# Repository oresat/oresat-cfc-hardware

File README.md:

# oresat-cfc-hardware

Cirrrus Flux Camera hardware repository. See also https://www.oresat.org/satellites/oresat/mission-2-cfc.

## General information
The Cirrus Flux Camera (CFC) is a Short Wave Infrared (SWIR) camera meant to map the global distribution of high-altitude cirrus clouds. It works by looking at the reflected sunlight from clouds in three SWIR bands. The primary investigators (PIs) for CFC calibration, data processing, and climate science are our collaborators at the [University of Maryland Baltimore Count (UMBC)'s Earth and Space Institute (ESI)](https://esi.umbc.edu/) as well as by our collaborators at the [University College London (UCL) Mullard Space Science Laboratory (MSSL)](https://www.ucl.ac.uk/mathematical-physical-sciences/mssl).

Older versions of the CFC flew on the [2022 NASA High Altitude Student Payload (HASP)](https://sg-webserver.phys.lsu.edu/) mission.

Different but modern versions were flown by [UMBC's AirHARP mission](https://esi.umbc.edu/airharp2-at-pace-pax/) on the NASA ER-2 high altitude plane.

Most recently, we flew a preliminary technology demonstration mission on [OreSat0.5](https://www.oresat.org/satellites/oresat0-5) launched August 16th, 2024.

We're planning on flying the science mission camera on OreSat1 in Q2 2026.

Versions of the CFC have also flown on the NASA High Altitude Student Payload (HASP) in New Mexico, and 
## Technical information about the CFC sensor

- Princeton IR PIRT1280 InGaAs focal plane array (1280 x 1024 with 12 um pixels), sensitive to roughly 800 - 1600 nm.
- We cool the sensor to -8 deg C using its built-in thermal electric cooler (TEC - just a standard Peltier device).
- We use three filters on the PIRT1280 sensors:
   - 870 nm: [Torrent Photonics Optical Filter Shop 2020OFS-870](https://opticalfiltershop.com/shop/bandpass-filter/nir-bandpass-700nm-to-1100nm/nir-bandpass-filter-870nm-fwhm-30nm/)
   - 1390 nm: [Torrent Photonics Optical Filter Shop 2020OFS-1390](https://opticalfiltershop.com/shop/bandpass-filter/swir-bandpass-filters-1-1um-to-3-0um/swir-bandpass-filter-1390nm-fwhm-35nm/)
   - 1590 nm: [Torrent Photonics Optical Filter Shop 2020OFS-1590](https://opticalfiltershop.com/shop/bandpass-filter/swir-bandpass-filters-1-1um-to-3-0um/swir-bandpass-filter-1590nm-fwhm-40nm/)
- Lens is the [Navitar SWIR-35](https://store.navitar.com/swir-35-35-mm/), a 35 mm  SWIR lens with focus adjustable apateur. 

## Technical information on the system

- The **CFC Sensor Card** is a PCB in backplane slot 18. It has:
   - The PIRT 1280 sensor soldered on the PCB
   - A custom machined lens adapter between the card and the lens.
   - Custom machined G10 L brackets between the custom machined lens adapter and slot 19 
   - The lens on the adapter sticks through the -Z end card, through the -Z end cap, and finally out into the tuna can volume. A 3D printed adapter on the End Card holds the monopole deployers and holds the camera lens at the End Card and End Cap levels.
   - The SWIR lens sticks into the tuna-can space on the -Z end of OreSat0.5 and OreSat1.
- The **CFC Processor Card** is a PCB in backplane slot 17 with:
   - LVDS to PRU adapter IC
   - an [Octavo OSD335x-SM](https://octavosystems.com/octavo_products/osd335x-sm/) system in package (SIP) processor with 1 GB DRAM and a 16 GB eMMC storage IC.
 - Radiator
    - The top of the CFC Sensor Card has a large block of copper being used as a heat spreader. The heat spreader dumps the heat from the TEC into thin copper leaf springs that lead the heat to two external copper radiators in the -Z+Y and -Z-Y solar module positions. These copper radiators are covered by a high emissivity tape.
    
## Design Notes

- Mostly on our Google Drive right now, here's the beginnings of our [CFC Design Notes](https://docs.google.com/document/d/1nDrTuUim9k1om3DOcBtnp3ixVvrmmALAsb2CZlDwwio/edit?usp=sharing).

## Links to CAD

- [OreSat CFC Camera mechnical in OnShape](https://cad.onshape.com/documents/0e986a82427039a7549eafca/v/f54f3484c685a75ab5bd82ce/e/deddd282159689e0e52f600b)
- [OreSat0.5 containing the CFC assembly in OnShape](https://cad.onshape.com/documents/c0a6cf3367d8fdcad3a3c2e1/w/ca55e3ec6f041493d70e4b39/e/591851cdc8c634aae1522f90)
- [Electronics CAD on Github](https://github.com/oresat/oresat-cfc-hardware) - mostly KiCad with some older EAGLE files.
- [Kernel module](https://github.com/oresat/oresat-prucam-pirt1280) for the PIRT 1280 on the Octavo's PRU.

## License

All materials in this repo are copyright Portland State Aerospace Society and are licensed under the CERN Open Hardware Licence Version 2 -
Strongly Reciprocal (CERN-OHL-S v2), or any later version. A copy of the license is located in [here](LICENSE.md).

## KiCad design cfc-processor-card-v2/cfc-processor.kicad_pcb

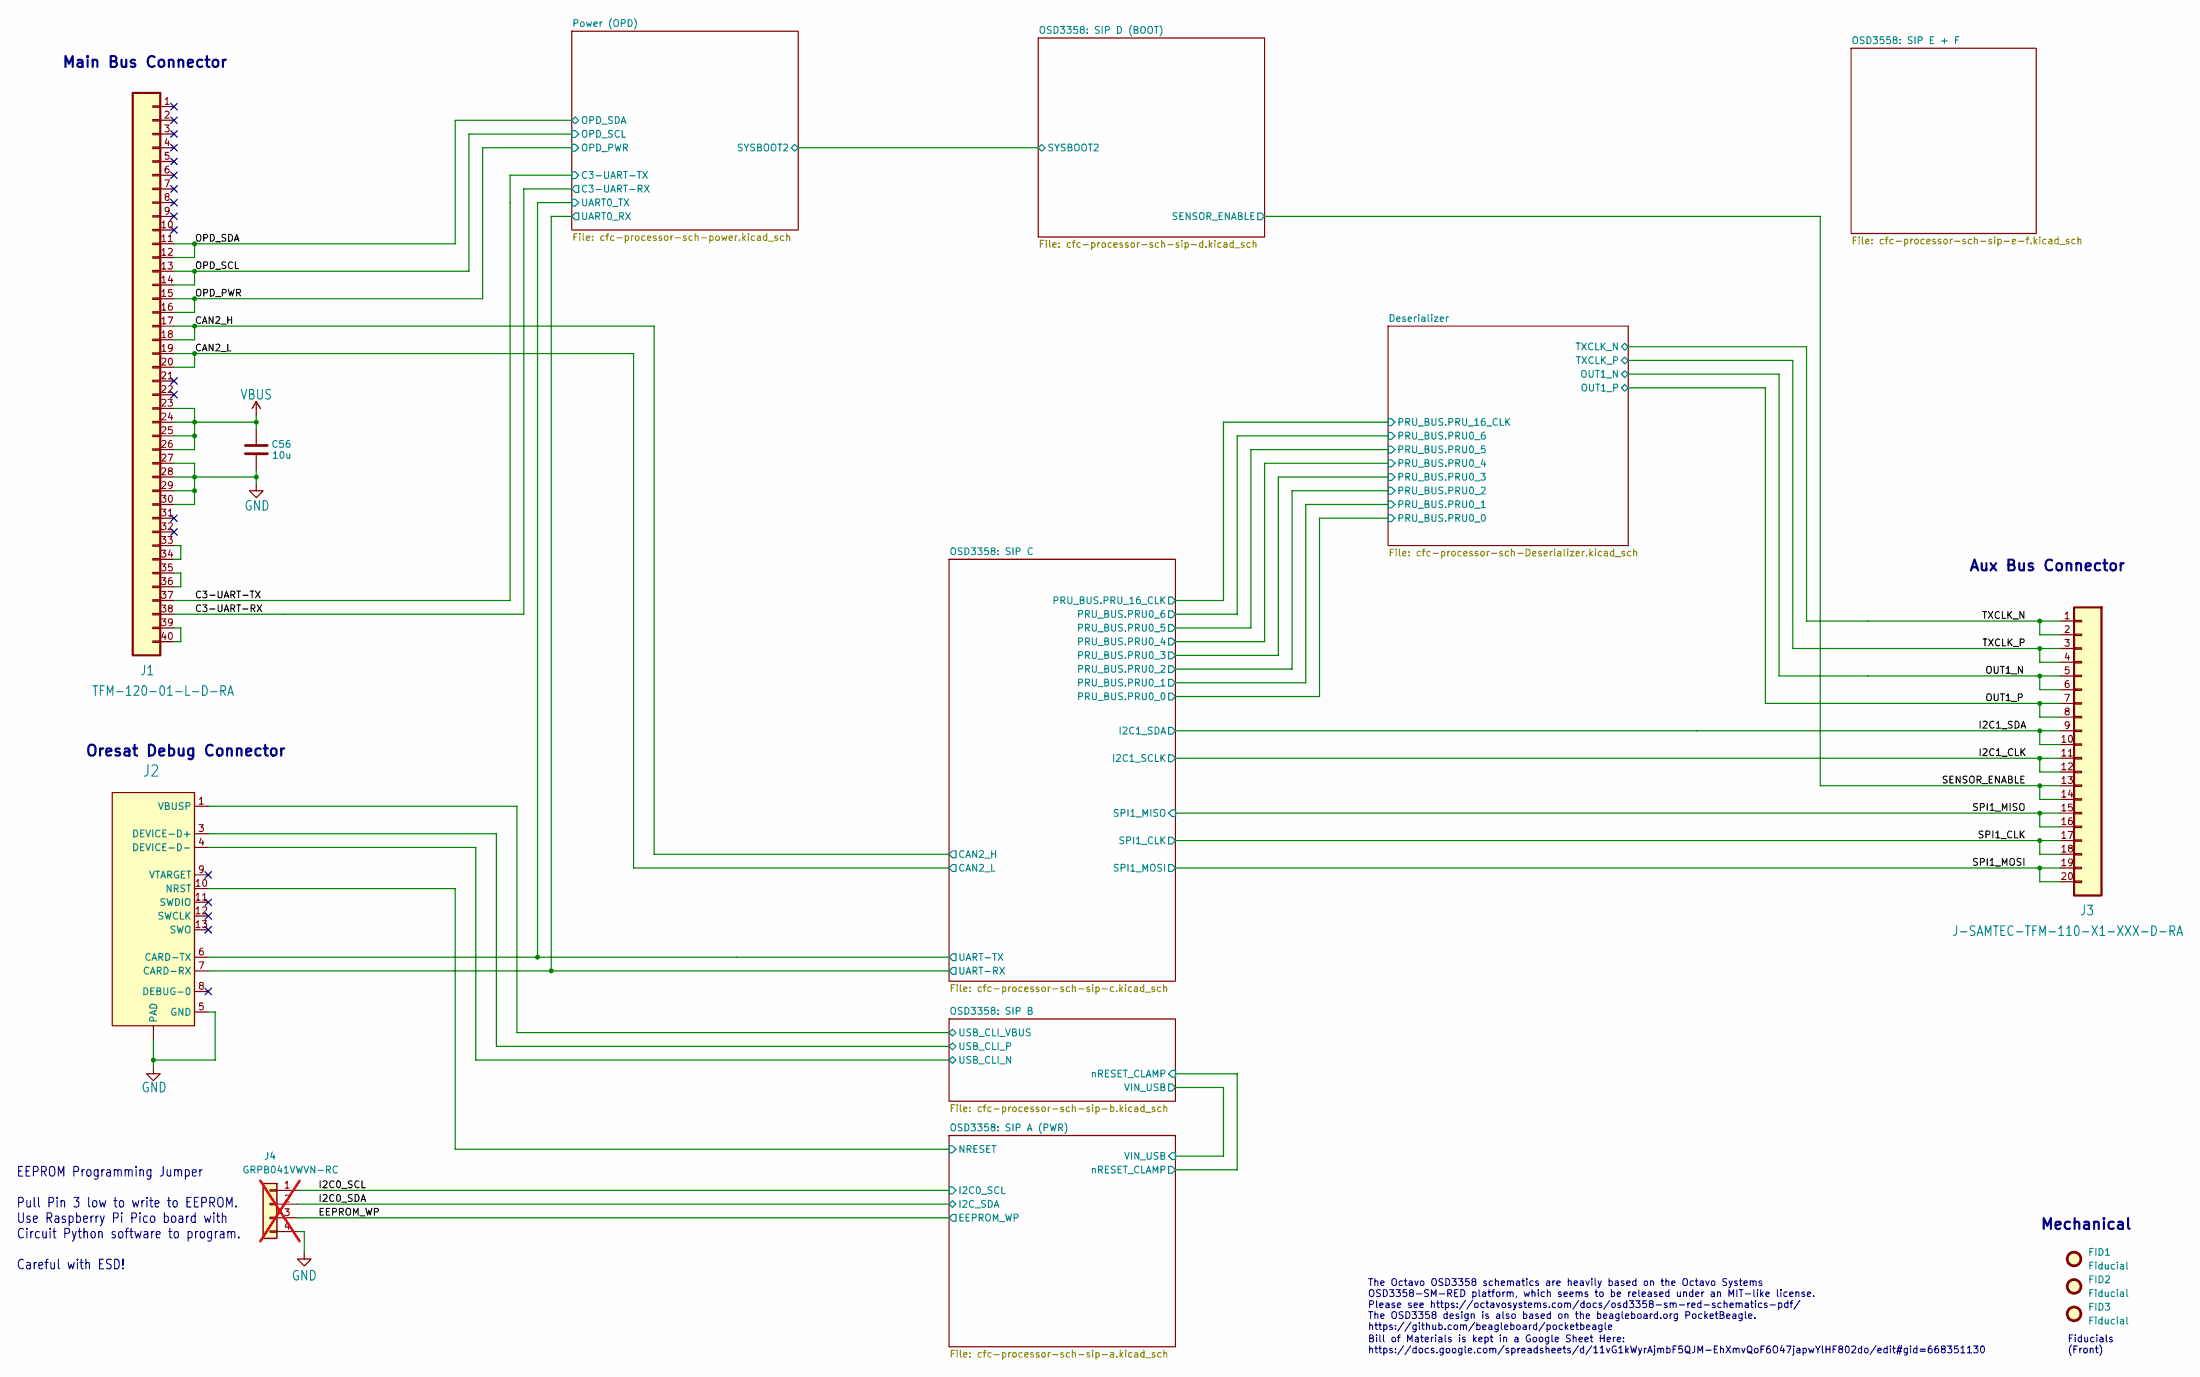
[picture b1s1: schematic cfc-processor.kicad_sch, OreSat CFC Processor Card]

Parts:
C56: 10u; 0805-B-NOSILK; MPN CL21B106KAYQNNE
FID1, FID2, FID3: Fiducial; Fiducial_1mm_Mask2mm
J1: TFM-120-01-L-D-RA; J-SAMTEC-TFM-120-X1-XXX-D-RA; MPN TFM-120-01-L-D-RA
J2: 2-1734592-0; J-JST-SM14BSHLSTF; MPN SM14B-SHLS-TF
J3: J-SAMTEC-TFM-110-X1-XXX-D-RA; MPN TFM-110-01-L-D-RA
J4: GRPB041VWVN-RC; PinHeader_1x04_P1.27mm_Vertical; MPN GRPB041VWVN-RC; not fitted

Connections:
/C3-UART-RX: J1.38; also elsewhere on the board
/C3-UART-TX: J1.37; also elsewhere on the board
/CAN2_H: J1.17, J1.18; also elsewhere on the board
/CAN2_L: J1.19, J1.20; also elsewhere on the board
/EEPROM_WP: J4.3; also elsewhere on the board
/I2C0_SCL: J4.1; also elsewhere on the board
/I2C0_SDA: J4.2; also elsewhere on the board
/I2C1_CLK: J3.11, J3.12; also elsewhere on the board
/I2C1_SDA: J3.9, J3.10; also elsewhere on the board
/OPD_PWR: J1.15, J1.16; also elsewhere on the board
/OPD_SCL: J1.13, J1.14; also elsewhere on the board
/OPD_SDA: J1.11, J1.12; also elsewhere on the board
/OSD3358: SIP A (PWR)/NRESET: J2.10 (NRST); also elsewhere on the board
/OSD3358: SIP B/USB_CLI_N: J2.4 (DEVICE-D-); also elsewhere on the board
/OSD3358: SIP B/USB_CLI_P: J2.3 (DEVICE-D+); also elsewhere on the board
/OSD3358: SIP B/USB_CLI_VBUS: J2.1 (VBUSP), J2.2 (VBUSP); also elsewhere on the board
/OSD3358: SIP C/UART-RX: J2.7 (CARD-RX); also elsewhere on the board
/OSD3358: SIP C/UART-TX: J2.6 (CARD-TX); also elsewhere on the board
/OUT1_N: J3.5, J3.6; also elsewhere on the board
/OUT1_P: J3.7, J3.8; also elsewhere on the board
/SENSOR_ENABLE: J3.13, J3.14; also elsewhere on the board
/SPI1_CLK: J3.17, J3.18; also elsewhere on the board
/SPI1_MISO: J3.15, J3.16; also elsewhere on the board
/SPI1_MOSI: J3.19, J3.20; also elsewhere on the board
/TXCLK_N: J3.1, J3.2; also elsewhere on the board
/TXCLK_P: J3.3, J3.4; also elsewhere on the board
GND: C56.2, J1.27, J1.28, J1.29, J1.30, J2.5 (GND), J2.14 (GND), J2.15 (PAD), J2.16 (PAD), J4.4; also elsewhere on the board
unnamed: J1.33, J1.34
unnamed: J1.35, J1.36
unnamed: J1.39, J1.40
VBUS: C56.1, J1.23, J1.24, J1.25, J1.26; also elsewhere on the board

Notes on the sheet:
Bill of Materials is kept in a Google Sheet Here: https://docs.google.com/spreadsheets/d/11vG1kWyrAjmbF5QJM-EhXmvQoF6O47japwYlHF802do/edit#gid=668351130
EEPROM Programming Jumper Pull Pin 3 low to write to EEPROM. Use Raspberry Pi Pico board with Circuit Python software to program. Careful with ESD!
The OSD3358 design is also based on the beagleboard.org PocketBeagle. https://github.com/beagleboard/pocketbeagle
Mechanical
Fiducials (Front)
Main Bus Connector
The Octavo OSD3358 schematics are heavily based on the Octavo Systems OSD3358-SM-RED platform, which seems to be released under an MIT-like license. Please see https://octavosystems.com/docs/osd3358-sm-red-schematics-pdf/
Aux Bus Connector
Oresat Debug Connector

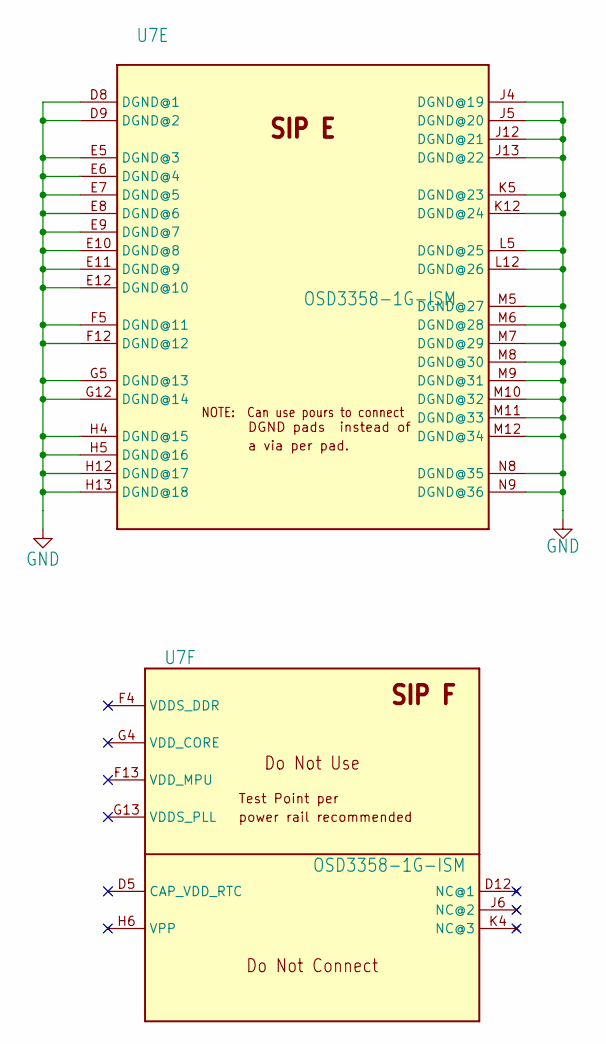
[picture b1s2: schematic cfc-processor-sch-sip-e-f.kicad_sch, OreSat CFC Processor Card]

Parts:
U7: OSD3358-1G-ISM; U-Octavo-OSD335X-BGA-256; MPN OSD3358-1G-ISM

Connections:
GND: U7.D8 (DGND@1), U7.D9 (DGND@2), U7.E5 (DGND@3), U7.E6 (DGND@4), U7.E7 (DGND@5), U7.E8 (DGND@6), U7.E9 (DGND@7), U7.E10 (DGND@8), U7.E11 (DGND@9), U7.E12 (DGND@10), U7.F5 (DGND@11), U7.F12 (DGND@12), U7.G5 (DGND@13), U7.G12 (DGND@14), U7.H4 (DGND@15), U7.H5 (DGND@16), U7.H12 (DGND@17), U7.H13 (DGND@18), U7.J4 (DGND@19), U7.J5 (DGND@20), U7.J12 (DGND@21), U7.J13 (DGND@22), U7.K5 (DGND@23), U7.K12 (DGND@24), U7.L5 (DGND@25), U7.L12 (DGND@26), U7.M5 (DGND@27), U7.M6 (DGND@28), U7.M7 (DGND@29), U7.M8 (DGND@30), U7.M9 (DGND@31), U7.M10 (DGND@32), U7.M11 (DGND@33), U7.M12 (DGND@34), U7.N8 (DGND@35), U7.N9 (DGND@36); also elsewhere on the board

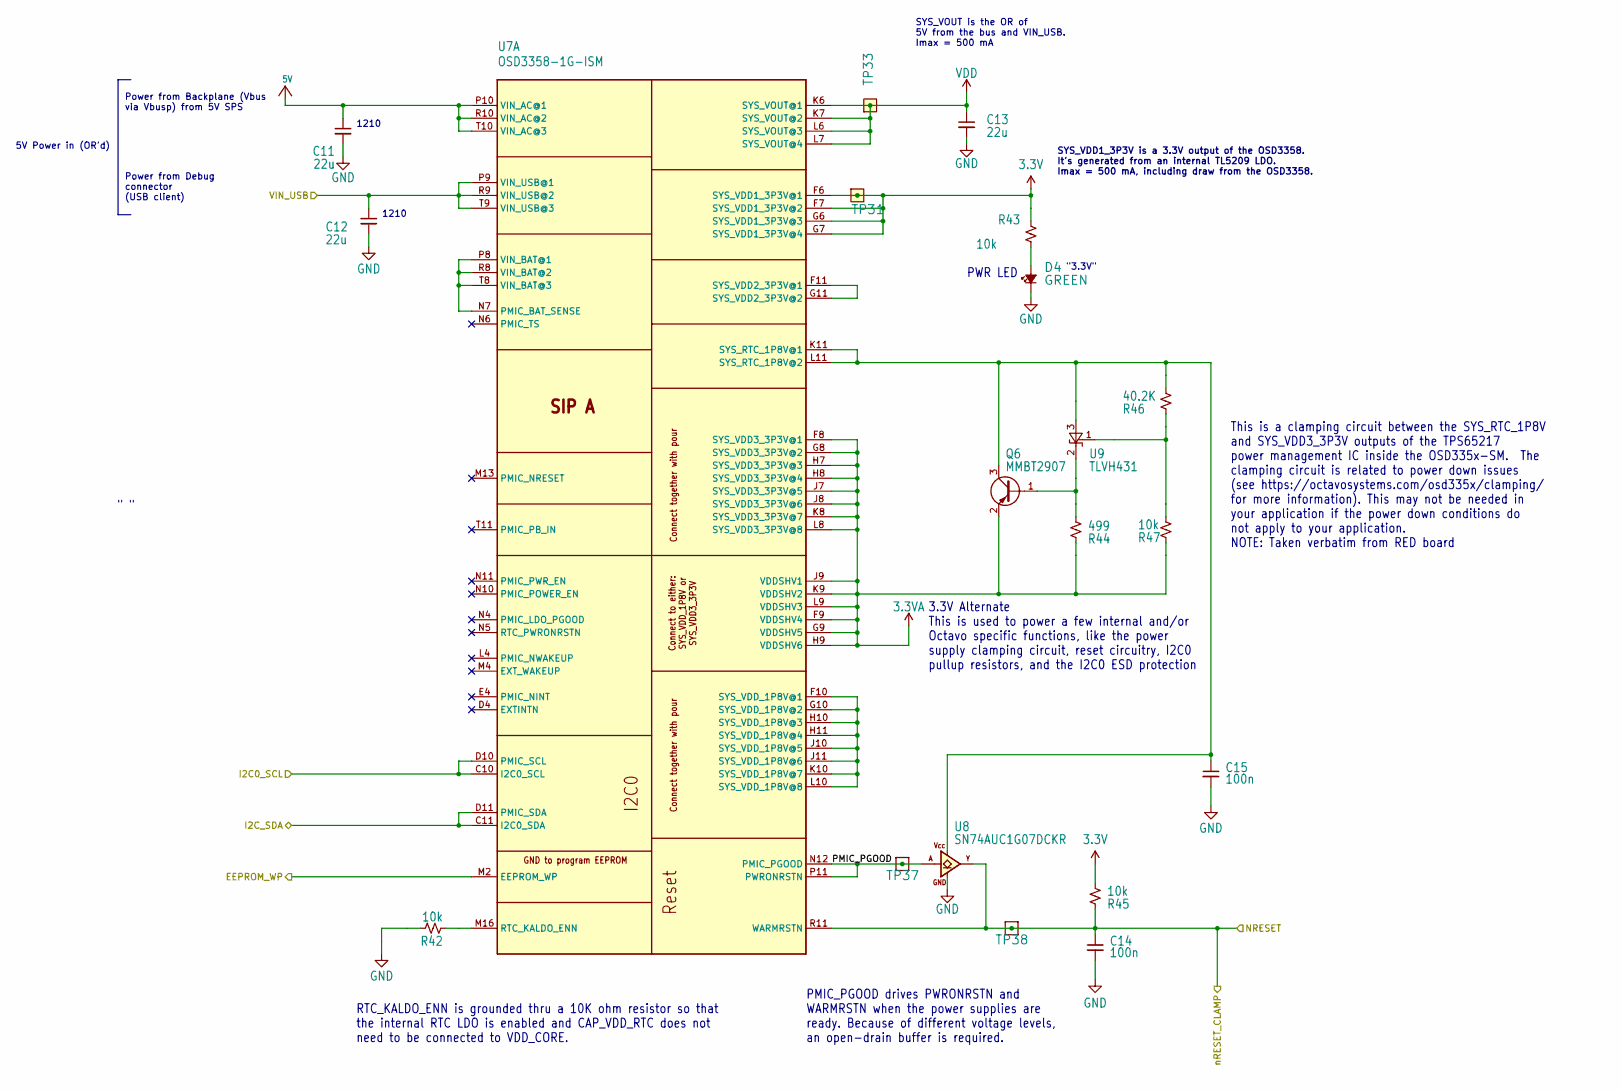
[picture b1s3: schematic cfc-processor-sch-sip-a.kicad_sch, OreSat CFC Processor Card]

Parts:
C11, C12, C13: 22u; C_1210_3225Metric; MPN TMK325B7226KMHP
C14, C15: 100n; 0603-C-NOSILK; MPN C0603C104K5RACAUTO
D4: GREEN; LED_0603_1608Metric; MPN 150060GS75000
Q6: MMBT2907; SOT-23; MPN PMBT2907A,235
R42, R43, R45, R47: 10k; 0603-C-NOSILK; MPN RMCF0603FT10K0
R44: 499; 0603-C-NOSILK; MPN RMCF0603FT499R
R46: 40.2K; 0603-C-NOSILK; MPN RMCF0603FT40K2
TP31: TEST-POINT; TestPoint-0.75mm-th
TP33: TEST-POINT3X4; TestPoint-0.75mm-th
TP37, TP38: TEST-POINT3X4; TestPoint_Pad_D1.0mm
U7: OSD3358-1G-ISM; U-Octavo-OSD335X-BGA-256; MPN OSD3358-1G-ISM
U8: SN74AUC1G07DCKR; SOT-353_SC-70-5; MPN SN74AUC1G07DCKR
U9: TLVH431; SOT-23; MPN TLVH431BCDBZT

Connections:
3.3V: R43.1, R45.1, TP31.1 (1_1), U7.F6 (SYS_VDD1_3P3V@1), U7.F7 (SYS_VDD1_3P3V@2), U7.G6 (SYS_VDD1_3P3V@3), U7.G7 (SYS_VDD1_3P3V@4); also elsewhere on the board
3.3VA: Q6.2 (E), R44.2, R47.2, U7.F8 (SYS_VDD3_3P3V@1), U7.F9 (VDDSHV4), U7.G8 (SYS_VDD3_3P3V@2), U7.G9 (VDDSHV5), U7.H7 (SYS_VDD3_3P3V@3), U7.H8 (SYS_VDD3_3P3V@4), U7.H9 (VDDSHV6), U7.J7 (SYS_VDD3_3P3V@5), U7.J8 (SYS_VDD3_3P3V@6), U7.J9 (VDDSHV1), U7.K8 (SYS_VDD3_3P3V@7), U7.K9 (VDDSHV2), U7.L8 (SYS_VDD3_3P3V@8), U7.L9 (VDDSHV3)
5V: C11.1, U7.P10 (VIN_AC@1), U7.R10 (VIN_AC@2), U7.T10 (VIN_AC@3); also elsewhere on the board
/EEPROM_WP: U7.M2 (EEPROM_WP); also elsewhere on the board
/I2C0_SCL: U7.C10 (I2C0_SCL), U7.D10 (PMIC_SCL); also elsewhere on the board
/I2C0_SDA: U7.C11 (I2C0_SDA), U7.D11 (PMIC_SDA); also elsewhere on the board
/OSD3358: SIP A (PWR)/NRESET: C14.1, R45.2, TP38.1 (1_1), U7.R11 (WARMRSTN), U8.4 (Y); also elsewhere on the board
/OSD3358: SIP A (PWR)/PMIC_PGOOD: TP37.1 (1_1), U7.N12 (PMIC_PGOOD), U7.P11 (PWRONRSTN), U8.2 (A)
/OSD3358: SIP A (PWR)/VIN_USB: C12.1, U7.P9 (VIN_USB@1), U7.R9 (VIN_USB@2), U7.T9 (VIN_USB@3); also elsewhere on the board
GND: C11.2, C12.2, C13.2, C14.2, C15.2, D4.1 (K), R42.1, U8.3 (GND); also elsewhere on the board
unnamed: D4.2 (A), R43.2
unnamed: Q6.1 (B), R44.1, U9.2 (K)
unnamed: C15.1, Q6.3 (C), R46.1, U7.K11 (SYS_RTC_1P8V@1), U7.L11 (SYS_RTC_1P8V@2), U8.5 (VCC), U9.3 (A)
unnamed: U7.N7 (PMIC_BAT_SENSE), U7.P8 (VIN_BAT@1), U7.R8 (VIN_BAT@2), U7.T8 (VIN_BAT@3)
unnamed: R42.2, U7.M16 (RTC_KALDO_ENN)
unnamed: U7.F11 (SYS_VDD2_3P3V@1), U7.G11 (SYS_VDD2_3P3V@2)
unnamed: U7.F10 (SYS_VDD_1P8V@1), U7.G10 (SYS_VDD_1P8V@2), U7.H10 (SYS_VDD_1P8V@3), U7.H11 (SYS_VDD_1P8V@4), U7.J10 (SYS_VDD_1P8V@5), U7.J11 (SYS_VDD_1P8V@6), U7.K10 (SYS_VDD_1P8V@7), U7.L10 (SYS_VDD_1P8V@8)
unnamed: R46.2, R47.1, U9.1 (REF)
VDD: C13.1, TP33.1 (1_1), U7.K6 (SYS_VOUT@1), U7.K7 (SYS_VOUT@2), U7.L6 (SYS_VOUT@3), U7.L7 (SYS_VOUT@4)

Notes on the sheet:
SYS_VDD1_3P3V is a 3.3V output of the OSD3358. It's generated from an internal TL5209 LDO. Imax = 500 mA, including draw from the OSD3358.
PMIC_PGOOD drives PWRONRSTN and WARMRSTN when the power supplies are ready. Because of different voltage levels, an open-drain buffer is required.
" "
5V Power in (OR'd)
RTC_KALDO_ENN is grounded thru a 10K ohm resistor so that the internal RTC LDO is enabled and CAP_VDD_RTC does not need to be connected to VDD_CORE.
This is a clamping circuit between the SYS_RTC_1P8V and SYS_VDD3_3P3V outputs of the TPS65217 power management IC inside the OSD335x-SM. The clamping circuit is related to power down issues (see https://octavosystems.com/osd335x/clamping/ for more information). This may not be needed in your applic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
"3.3V"
PWR LED
1210
SYS_VOUT is the OR of 5V from the bus and VIN_USB. Imax = 500 mA
Power from Debug connector (USB client)
3.3V Alternate This is used to power a few internal and/or Octavo specific functions, like the power supply clamping circuit, reset circuitry, I2C0 pullup resistors, and the I2C0 ESD protection
Power from Backplane (Vbus via Vbusp) from 5V SPS

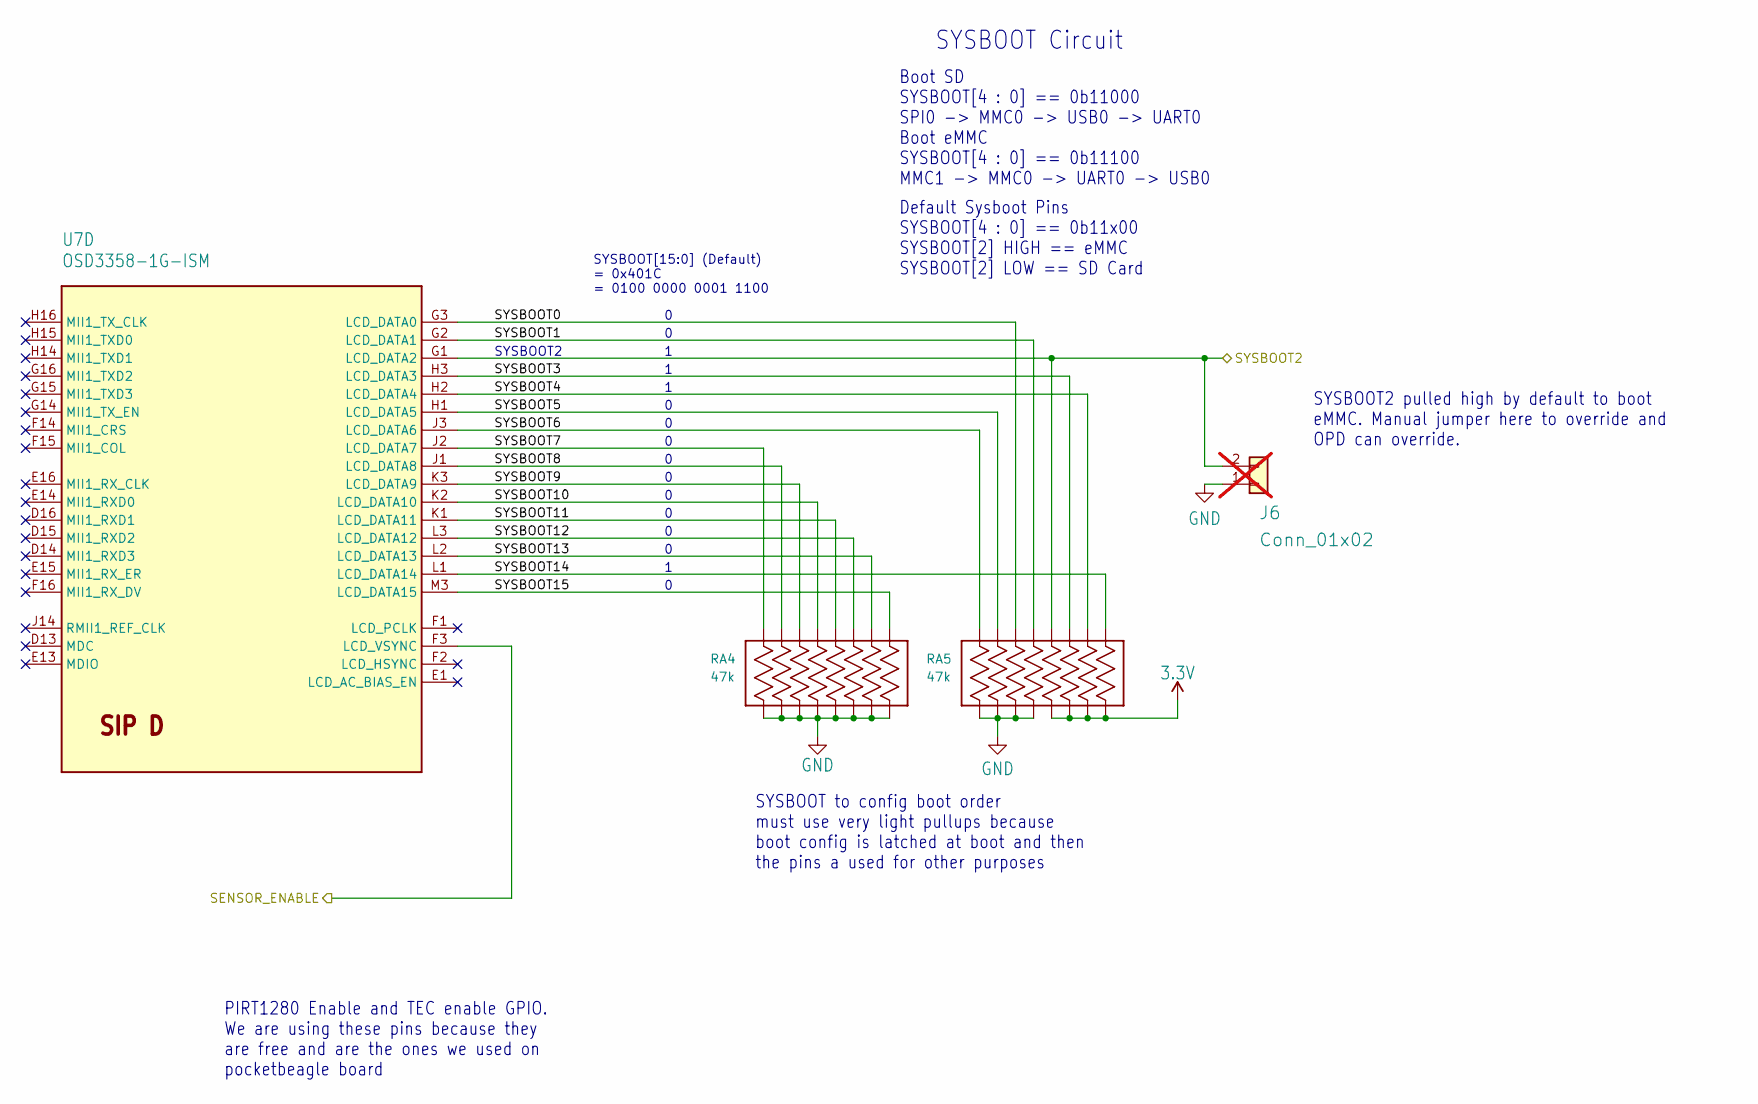
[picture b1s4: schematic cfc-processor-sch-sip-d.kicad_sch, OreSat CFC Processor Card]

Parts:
J6: Conn_01x02; PinHeader_1x02_P2.54mm_Vertical; not fitted
RA4, RA5: 47k; RES_EXB2HV; MPN EXB-2HV473JV
U7: OSD3358-1G-ISM; U-Octavo-OSD335X-BGA-256; MPN OSD3358-1G-ISM

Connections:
3.3V: RA5.5, RA5.6, RA5.7, RA5.8; also elsewhere on the board
/OSD3358: SIP D (BOOT)/SYSBOOT0: RA5.14, U7.G3 (LCD_DATA0)
/OSD3358: SIP D (BOOT)/SYSBOOT1: RA5.13, U7.G2 (LCD_DATA1)
/OSD3358: SIP D (BOOT)/SYSBOOT2: J6.2, RA5.12, U7.G1 (LCD_DATA2); also elsewhere on the board
/OSD3358: SIP D (BOOT)/SYSBOOT3: RA5.11, U7.H3 (LCD_DATA3)
/OSD3358: SIP D (BOOT)/SYSBOOT4: RA5.10, U7.H2 (LCD_DATA4)
/OSD3358: SIP D (BOOT)/SYSBOOT5: RA5.15, U7.H1 (LCD_DATA5)
/OSD3358: SIP D (BOOT)/SYSBOOT6: RA5.16, U7.J3 (LCD_DATA6)
/OSD3358: SIP D (BOOT)/SYSBOOT7: RA4.16, U7.J2 (LCD_DATA7)
/OSD3358: SIP D (BOOT)/SYSBOOT8: RA4.15, U7.J1 (LCD_DATA8)
/OSD3358: SIP D (BOOT)/SYSBOOT9: RA4.14, U7.K3 (LCD_DATA9)
/OSD3358: SIP D (BOOT)/SYSBOOT10: RA4.13, U7.K2 (LCD_DATA10)
/OSD3358: SIP D (BOOT)/SYSBOOT11: RA4.12, U7.K1 (LCD_DATA11)
/OSD3358: SIP D (BOOT)/SYSBOOT12: RA4.11, U7.L3 (LCD_DATA12)
/OSD3358: SIP D (BOOT)/SYSBOOT13: RA4.10, U7.L2 (LCD_DATA13)
/OSD3358: SIP D (BOOT)/SYSBOOT14: RA5.9, U7.L1 (LCD_DATA14)
/OSD3358: SIP D (BOOT)/SYSBOOT15: RA4.9, U7.M3 (LCD_DATA15)
/SENSOR_ENABLE: U7.F3 (LCD_VSYNC); also elsewhere on the board
GND: J6.1, RA4.1, RA4.2, RA4.3, RA4.4, RA4.5, RA4.6, RA4.7, RA4.8, RA5.1, RA5.2, RA5.3, RA5.4; also elsewhere on the board

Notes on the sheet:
PIRT1280 Enable and TEC enable GPIO. We are using these pins because they are free and are the ones we used on pocketbeagle board
SYSBOOT Circuit
SYSBOOT[15:0] (Default) = 0x401C = 0100 0000 0001 1100
Boot SD SYSBOOT[4 : 0] == 0b11000 SPI0 -> MMC0 -> USB0 -> UART0 Boot eMMC SYSBOOT[4 : 0] == 0b11100 MMC1 -> MMC0 -> UART0 -> USB0
Default Sysboot Pins SYSBOOT[4 : 0] == 0b11x00 SYSBOOT[2] HIGH == eMMC SYSBOOT[2] LOW == SD Card
SYSBOOT to config boot order must use very light pullups because boot config is latched at boot and then the pins a used for other purposes
SYSBOOT2 pulled high by default to boot eMMC. Manual jumper here to override and OPD can override.
SYSBOOT2

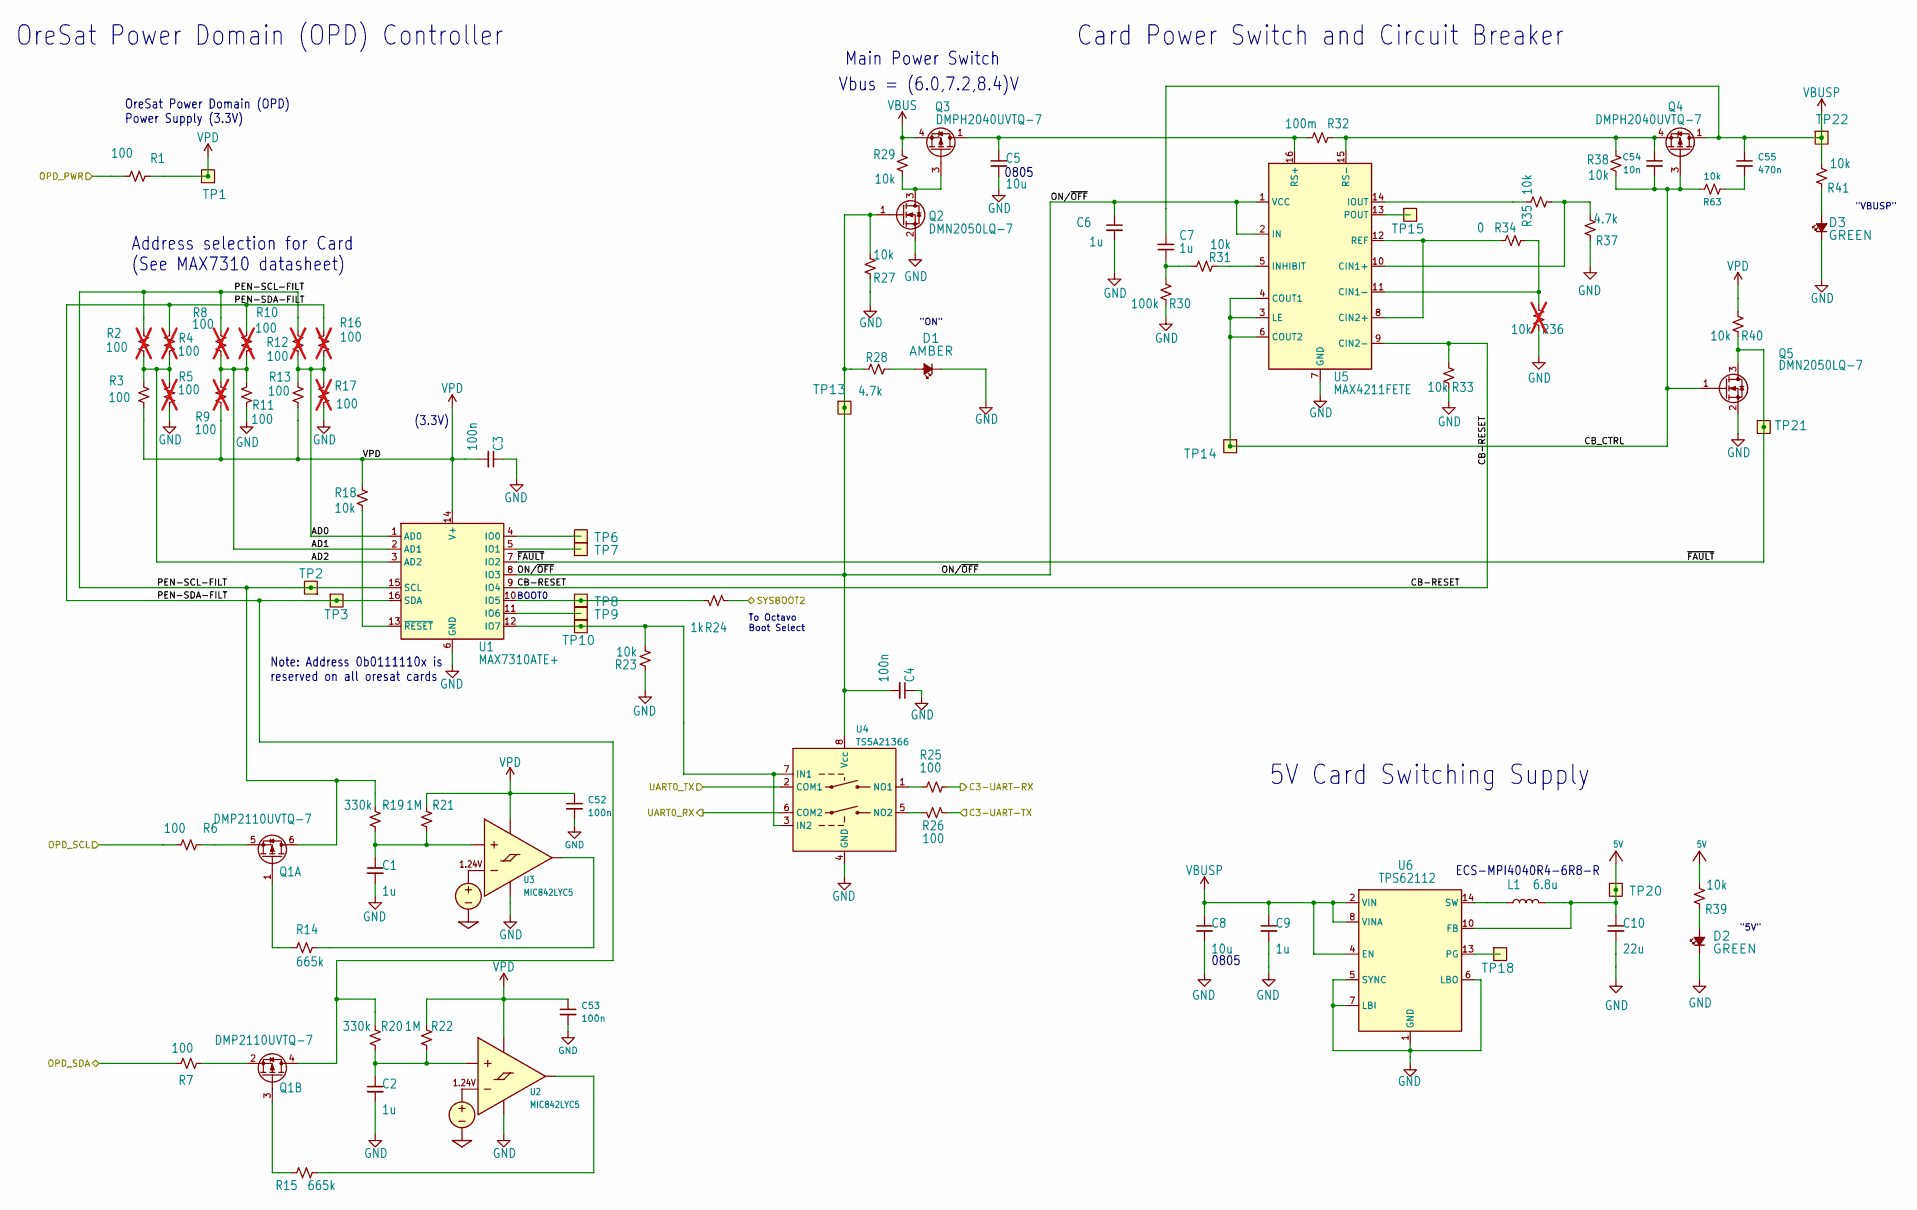
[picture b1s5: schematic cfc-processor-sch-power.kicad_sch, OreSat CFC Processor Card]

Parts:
C1, C2, C6, C7, C9: 1u; 0603-C-NOSILK; MPN GCM21BR71H105KA03L
C3, C4, C52, C53: 100n; 0603-C-NOSILK; MPN C0603C104K5RACAUTO
C5, C8: 10u; 0805-C-NOSILK; MPN GRT21BC71E106KE13K
C10: 22u; C_1210_3225Metric; MPN TMK325B7226KMHP
C54: 10n; 0603-C-NOSILK; MPN C0603C103J5RACAUTO
C55: 470n; 0603-C-NOSILK; MPN C0603C474K3RACAUTO
D1: AMBER; LED_0603_1608Metric; MPN 150060AS75000
D2, D3: GREEN; LED_0603_1608Metric; MPN 150060GS75000
L1: 6.8u; L_ECS-MPI4040; MPN ECS-MPI4040R4-6R8-R
Q1: DMP2110UVTQ-7; SOT-23-6; MPN DMP2110UVTQ-7
Q2, Q5: DMN2050LQ-7; SOT-23; MPN DMN2050LQ-7
Q3, Q4: DMPH2040UVTQ-7; TSOT-23-6; MPN DMPH2040UVTQ-7
R1, R3, R6, R7, R11, R13, R25, R26: 100; 0603-C-NOSILK; MPN RMCF0603FT100R
R2, R4, R5, R8, R9, R10, R12, R16, R17: 100; 0603-C-NOSILK; MPN RMCF0603FT100R; not fitted
R14, R15: 665k; 0603-C-NOSILK; MPN RMCF0603FT665K
R18, R23, R27, R29, R31, R33, R35, R38, R39, R40, R41, R63: 10k; 0603-C-NOSILK; MPN RMCF0603FT10K0
R19, R20: 330k; 0603-C-NOSILK; MPN RMCF0603FT330K
R21, R22: 1M; 0603-C-NOSILK; MPN RMCF0603FG1M00
R24: 1k; 0603-C-NOSILK; MPN RMCF0603FT1K00
R28, R37: 4.7k; 0603-C-NOSILK; MPN RMCF0603FT4K70
R30: 100k; 0603-C-NOSILK; MPN RMCF0603FT100K
R32: 100m; 1206-C; MPN CSR1206FTR100
R34: 0; 0603-C-NOSILK; MPN RMCF0603ZT0R00
R36: 10k; 0603-C-NOSILK; MPN RC1005F6653CS; not fitted
TP1, TP2, TP3, TP6, TP7, TP8, TP9, TP10, TP13, TP14, TP15, TP18, TP20, TP21, TP22: TEST-POINT; TestPoint-0.75mm-th
U1: MAX7310ATE+; QFN-16-1EP_4x4mm_P0.65mm_EP2.1x2.1mm; MPN MAX7310ATE+
U2, U3: MIC842LYC5; SOT-353_SC-70-5; MPN MIC842LYC5-TR
U4: TS5A21366; VSSOP-8_2.3x2mm_P0.5mm; MPN TS5A21366DCUR
U5: MAX4211FETE; QFN-16-1EP_4x4mm_P0.65mm_EP2.1x2.1mm; MPN MAX4211FETE
U6: TPS62112; Texas_RSA_VQFN-16-1EP_4x4mm_P0.65mm_EP2.7x2.7mm; MPN TPS62112RSAR

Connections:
5V: C10.1, L1.2, R39.2, TP20.1 (1_1), U6.10 (FB); also elsewhere on the board
/C3-UART-RX: R25.1; also elsewhere on the board
/C3-UART-TX: R26.2; also elsewhere on the board
/OPD_PWR: R1.1; also elsewhere on the board
/OPD_SCL: R6.1; also elsewhere on the board
/OPD_SDA: R7.1; also elsewhere on the board
/OSD3358: SIP C/UART-RX: U4.6 (COM2); also elsewhere on the board
/OSD3358: SIP C/UART-TX: U4.2 (COM1); also elsewhere on the board
/OSD3358: SIP D (BOOT)/SYSBOOT2: R24.2; also elsewhere on the board
/Power (OPD)/AD0: R12.2, R13.1, R16.2, R17.1, U1.1 (AD0)
/Power (OPD)/AD1: R8.2, R9.1, R10.2, R11.1, U1.2 (AD1)
/Power (OPD)/AD2: R2.2, R3.1, R4.2, R5.1, U1.3 (AD2)
/Power (OPD)/CB-RESET: R33.2, U1.9 (IO4), U5.9 (CIN2-)
/Power (OPD)/CB_CTRL: C54.2, Q4.3 (G), Q5.1 (G), R38.1, R63.2, TP14.1 (1_1), U5.3 (LE), U5.4 (COUT1), U5.6 (COUT2)
/Power (OPD)/ON/~OFF: C4.2, C6.1, Q2.1 (G), R27.2, R28.2, TP13.1 (1_1), U1.8 (IO3), U4.8 (Vcc), U5.1 (VCC), U5.2 (IN)
/Power (OPD)/PEN-SCL-FILT: Q1.6 (D), R2.1, R8.1, R12.1, R19.2, TP2.1 (1_1), U1.15 (SCL)
/Power (OPD)/PEN-SDA-FILT: Q1.4 (D), R4.1, R10.1, R16.1, R20.2, TP3.1 (1_1), U1.16 (SDA)
/Power (OPD)/~FAULT: Q5.3 (D), R40.1, TP21.1 (1_1), U1.7 (IO2)
GND: C1.2, C2.2, C3.1, C4.1, C5.2, C6.2, C8.2, C9.2, C10.2, C52.2, C53.2, D1.1 (K), D2.1 (K), D3.1 (K), Q2.2 (S), Q5.2 (S), R5.2, R11.2, R17.2, R23.1, R27.1, R30.1, R33.1, R36.1, R37.1, U1.6 (GND), U1.17 (GND), U2.2 (GND), U3.2 (GND), U4.4 (GND), U5.7 (GND), U5.17 (GND), U6.1 (GND), U6.5 (SYNC), U6.6 (LBO), U6.7 (LBI), U6.9 (GND), U6.11 (GND), U6.12 (GND), U6.16 (GND), U6.17 (GND); also elsewhere on the board
unnamed: C7.1, R30.2, R31.2
unnamed: C55.2, R63.1
unnamed: D1.2 (A), R28.1
unnamed: D2.2 (A), R39.1
unnamed: D3.2 (A), R41.1
unnamed: L1.1, U6.14 (SW), U6.15 (SW)
unnamed: Q1.1 (G), R14.2
unnamed: Q1.5 (S), R6.2
unnamed: Q1.3 (G), R15.2
unnamed: Q1.2 (S), R7.2
unnamed: Q2.3 (D), Q3.3 (G), R29.1
unnamed: C54.1, Q4.4 (S), R32.2, R38.2, U5.15 (RS-)
unnamed: TP6.1 (1_1), U1.4 (IO0)
unnamed: TP7.1 (1_1), U1.5 (IO1)
unnamed: R24.1, TP8.1 (1_1), U1.10 (IO5)
unnamed: TP9.1 (1_1), U1.11 (IO6)
unnamed: R23.2, TP10.1 (1_1), U1.12 (IO7), U4.3 (IN2), U4.7 (IN1)
unnamed: R18.1, U1.13 (~RESET)
unnamed: C2.1, R20.1, R22.1, U2.1 (INP)
unnamed: R15.1, U2.4 (OUT)
unnamed: C1.1, R19.1, R21.1, U3.1 (INP)
unnamed: R14.1, U3.4 (OUT)
unnamed: R25.2, U4.1 (NO1)
unnamed: R26.1, U4.5 (NO2)
unnamed: R35.1, R37.2, U5.10 (CIN1+)
unnamed: R34.1, R36.2, U5.11 (CIN1-)
unnamed: R34.2, U5.8 (CIN2+), U5.12 (REF)
unnamed: R31.1, U5.5 (INHIBIT)
unnamed: R35.2, U5.14 (IOUT)
unnamed: TP15.1 (1_1), U5.13 (POUT)
unnamed: C5.1, Q3.1 (D), Q3.2 (D), Q3.5 (D), Q3.6 (D), R32.1, U5.16 (RS+)
unnamed: TP18.1 (1_1), U6.13 (PG)
VBUS: Q3.4 (S), R29.2; also elsewhere on the board
VBUSP: C7.2, C8.1, C9.1, C55.1, Q4.1 (D), Q4.2 (D), Q4.5 (D), Q4.6 (D), R41.2, TP22.1 (1_1), U6.2 (VIN), U6.3 (VIN), U6.4 (EN), U6.8 (VINA)
VPD: C3.2, C52.1, C53.1, R1.2, R3.2, R9.2, R13.2, R18.2, R21.2, R22.2, R40.2, TP1.1 (1_1), U1.14 (V+), U2.5 (VDD), U3.5 (VDD)

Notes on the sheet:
0805
Card Power Switch and Circuit Breaker
BOOT0
Main Power Switch
OreSat Power Domain (OPD) Controller
"ON"
"5V"
ECS-MPI4040R4-6R8-R
(3.3V)
OreSat Power Domain (OPD) Power Supply (3.3V)
Address selection for Card (See MAX7310 datasheet)
To Octavo Boot Select
Vbus = (6.0,7.2,8.4)V
"VBUSP"
5V Card Switching Supply
Note: Address 0b0111110x is reserved on all oresat cards
